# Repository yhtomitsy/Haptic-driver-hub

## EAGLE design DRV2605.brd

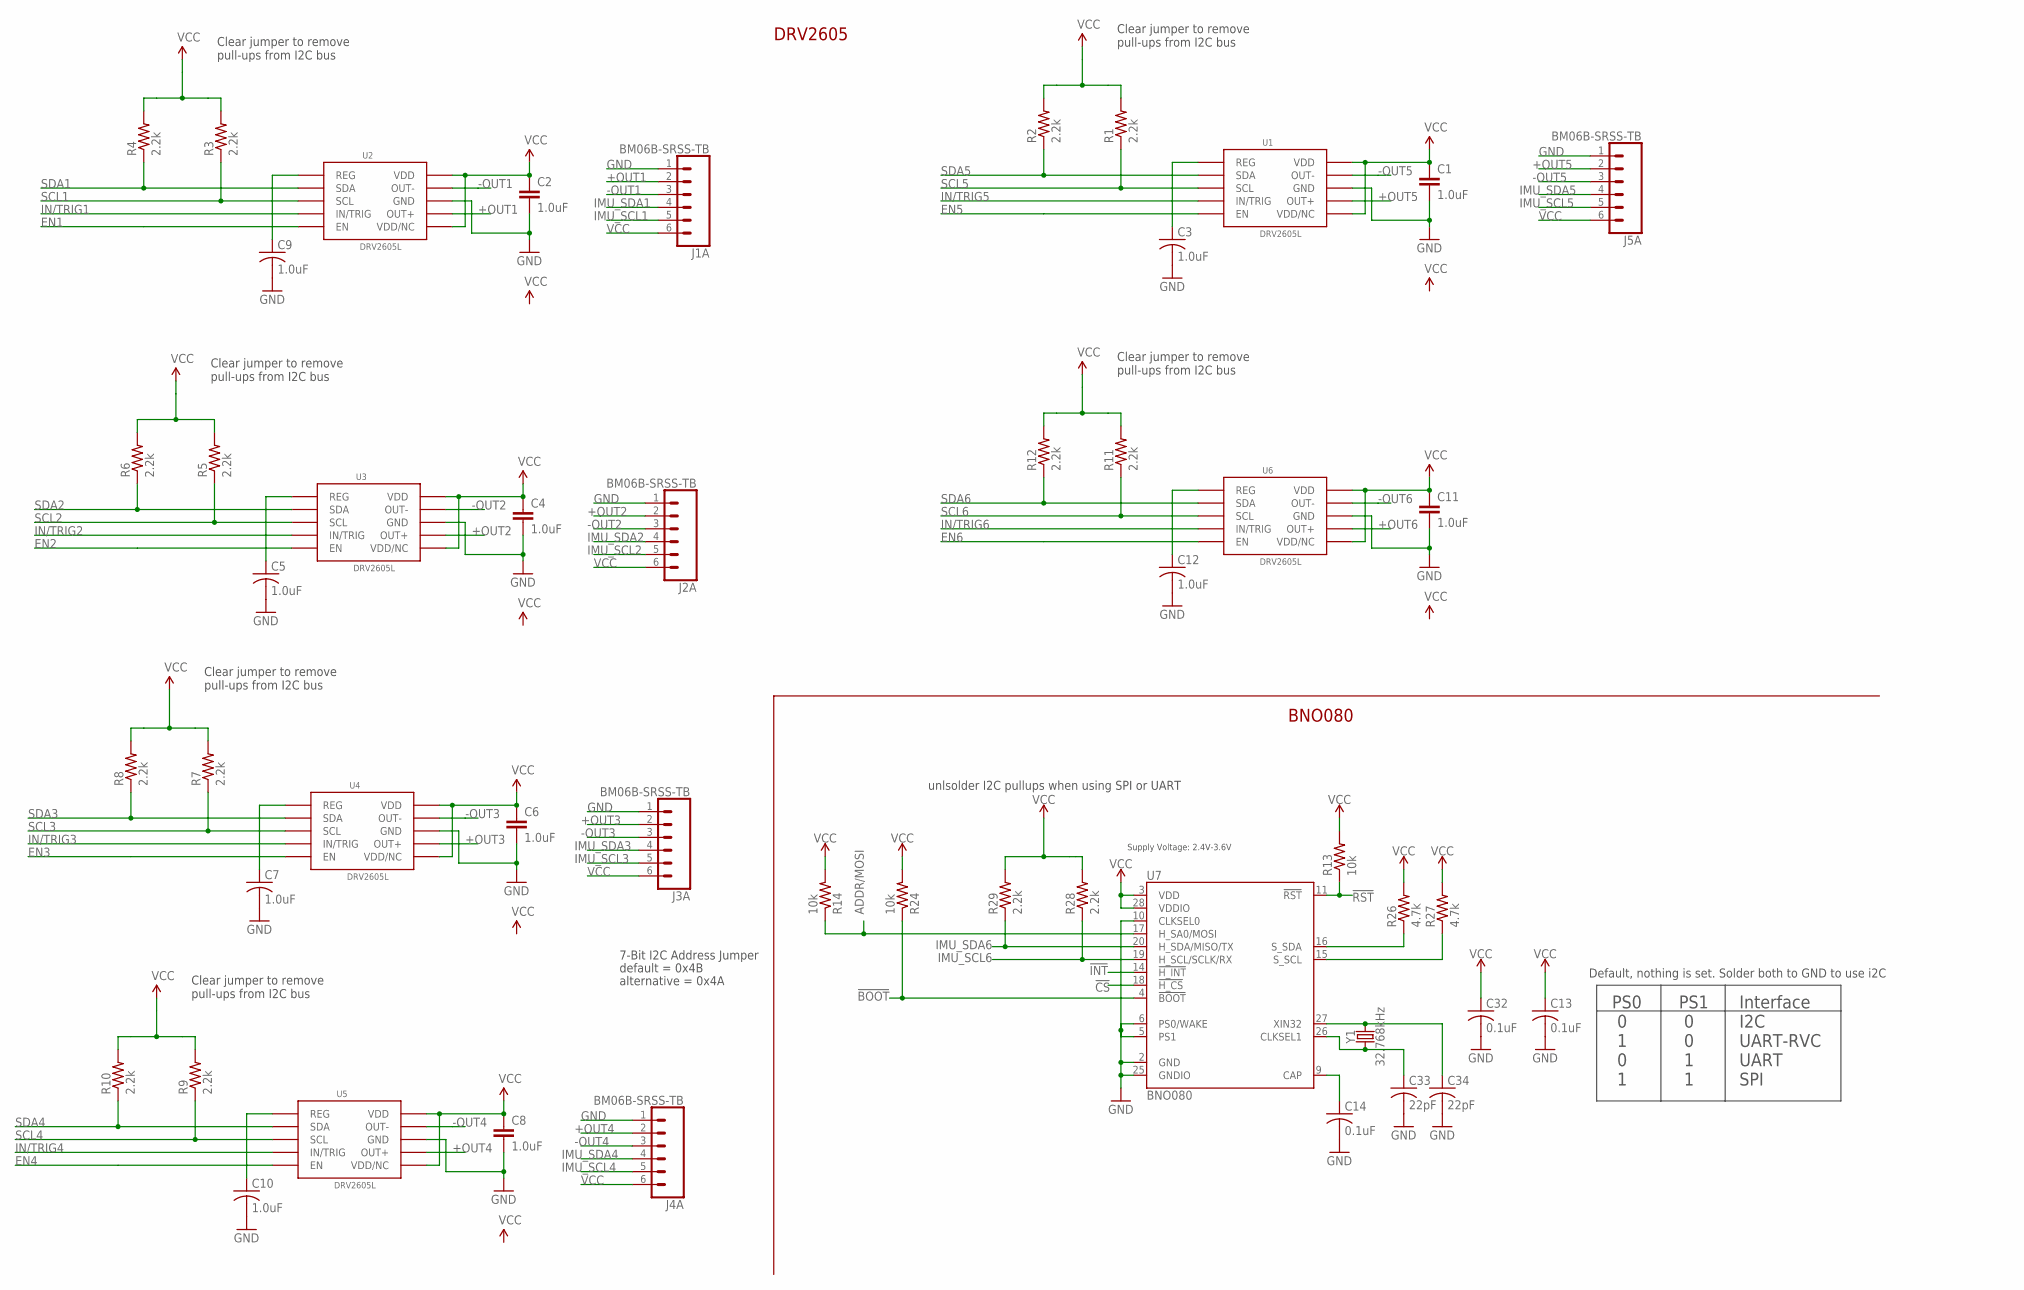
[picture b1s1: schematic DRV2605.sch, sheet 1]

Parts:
C1, C2, C4, C6, C8, C11: 1.0uF; 0402-CAP
C3, C5, C7, C9, C10, C12: 1.0uF; C0402
C13, C14, C32: 0.1uF; C0402
C33, C34: 22pF; C0402
J1, J2, J3, J4, J5: BM06B-SRSS-TB; JST-6-SMD-HORI-1.0MM
R1, R2, R3, R4, R5, R6, R7, R8, R9, R10, R11, R12: 2.2k; 0603-RES
R13, R14, R24: 10k; R0402
R26, R27: 4.7k; R0402
R28, R29: 2.2k; R0402
U1, U2, U3, U4, U5, U6: DRV2605L; VSSOP-10
U7: BNO080; LGA-28
Y1: 32.768kHz; CRYSTAL-SMD-3.2X1.5MM

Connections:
!BOOT: R24.1, U7.4 (!BOOT)
!CS: U7.18 (!H_CS)
!INT: U7.14 (!H_INT)
!RST: R13.1, U7.11 (!RST)
+OUT1: J1.2, U2.P$7 (OUT+)
+OUT2: J2.2, U3.P$7 (OUT+)
+OUT3: J3.2, U4.P$7 (OUT+)
+OUT4: J4.2, U5.P$7 (OUT+)
+OUT5: J5.2, U1.P$7 (OUT+)
+OUT6: U6.P$7 (OUT+); also elsewhere on the board
-OUT1: J1.3, U2.P$9 (OUT-)
-OUT2: J2.3, U3.P$9 (OUT-)
-OUT3: J3.3, U4.P$9 (OUT-)
-OUT4: J4.3, U5.P$9 (OUT-)
-OUT5: J5.3, U1.P$9 (OUT-)
-OUT6: U6.P$9 (OUT-); also elsewhere on the board
ADDR/MOSI: R14.1, U7.17 (H_SA0/MOSI)
CAP: C14.1, U7.9 (CAP)
EN1: U2.P$5 (EN); also elsewhere on the board
EN2: U3.P$5 (EN); also elsewhere on the board
EN3: U4.P$5 (EN); also elsewhere on the board
EN4: U5.P$5 (EN); also elsewhere on the board
EN5: U1.P$5 (EN); also elsewhere on the board
EN6: U6.P$5 (EN); also elsewhere on the board
GND: C1.2, C2.2, C3.2, C4.2, C5.2, C6.2, C7.2, C8.2, C9.2, C10.2, C11.2, C12.2, C13.2, C14.2, C32.2, C33.2, C34.2, J1.1, J2.1, J3.1, J4.1, J5.1, U1.P$8 (GND), U2.P$8 (GND), U3.P$8 (GND), U4.P$8 (GND), U5.P$8 (GND), U6.P$8 (GND), U7.2 (GND), U7.5 (PS1), U7.6 (PS0/WAKE), U7.10 (CLKSEL0), U7.25 (GNDIO); also elsewhere on the board
IMU_SCL1: J1.5; also elsewhere on the board
IMU_SCL2: J2.5; also elsewhere on the board
IMU_SCL3: J3.5; also elsewhere on the board
IMU_SCL4: J4.5; also elsewhere on the board
IMU_SCL5: J5.5; also elsewhere on the board
IMU_SCL6: R28.1, U7.19 (H_SCL/SCLK/RX); also elsewhere on the board
IMU_SDA1: J1.4; also elsewhere on the board
IMU_SDA2: J2.4; also elsewhere on the board
IMU_SDA3: J3.4; also elsewhere on the board
IMU_SDA4: J4.4; also elsewhere on the board
IMU_SDA5: J5.4; also elsewhere on the board
IMU_SDA6: R29.1, U7.20 (H_SDA/MISO/TX); also elsewhere on the board
IN/TRIG1: U2.P$4 (IN/TRIG); also elsewhere on the board
IN/TRIG2: U3.P$4 (IN/TRIG); also elsewhere on the board
IN/TRIG3: U4.P$4 (IN/TRIG); also elsewhere on the board
IN/TRIG4: U5.P$4 (IN/TRIG); also elsewhere on the board
IN/TRIG5: U1.P$4 (IN/TRIG); also elsewhere on the board
IN/TRIG6: U6.P$4 (IN/TRIG); also elsewhere on the board
unnamed: C3.1, U1.P$1 (REG)
unnamed: C12.1, U6.P$1 (REG)
unnamed: C34.1, U7.27 (XIN32), Y1.P$2 (2)
unnamed: C9.1, U2.P$1 (REG)
unnamed: C5.1, U3.P$1 (REG)
unnamed: C33.1, U7.26 (CLKSEL1), Y1.P$1 (1)
unnamed: C7.1, U4.P$1 (REG)
unnamed: C10.1, U5.P$1 (REG)
SCL1: R3.1, U2.P$2 (SCL); also elsewhere on the board
SCL2: R5.1, U3.P$2 (SCL); also elsewhere on the board
SCL3: R7.1, U4.P$2 (SCL); also elsewhere on the board
SCL4: R9.1, U5.P$2 (SCL); also elsewhere on the board
SCL5: R1.1, U1.P$2 (SCL); also elsewhere on the board
SCL6: R11.1, U6.P$2 (SCL); also elsewhere on the board
SDA1: R4.1, U2.P$3 (SDA); also elsewhere on the board
SDA2: R6.1, U3.P$3 (SDA); also elsewhere on the board
SDA3: R8.1, U4.P$3 (SDA); also elsewhere on the board
SDA4: R10.1, U5.P$3 (SDA); also elsewhere on the board
SDA5: R2.1, U1.P$3 (SDA); also elsewhere on the board
SDA6: R12.1, U6.P$3 (SDA); also elsewhere on the board
S_SCL: R27.1, U7.15 (S_SCL)
S_SDA: R26.1, U7.16 (S_SDA)
VCC: C1.1, C2.1, C4.1, C6.1, C8.1, C11.1, C13.1, C32.1, J1.6, J2.6, J3.6, J4.6, J5.6, R1.2, R2.2, R3.2, R4.2, R5.2, R6.2, R7.2, R8.2, R9.2, R10.2, R11.2, R12.2, R13.2, R14.2, R24.2, R26.2, R27.2, R28.2, R29.2, U1.P$6 (VDD/NC), U1.P$10 (VDD), U2.P$6 (VDD/NC), U2.P$10 (VDD), U3.P$6 (VDD/NC), U3.P$10 (VDD), U4.P$6 (VDD/NC), U4.P$10 (VDD), U5.P$6 (VDD/NC), U5.P$10 (VDD), U6.P$6 (VDD/NC), U6.P$10 (VDD), U7.3 (VDD), U7.28 (VDDIO); also elsewhere on the board

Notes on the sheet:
Clear jumper to remove pull-ups from I2C bus
7-Bit I2C Address Jumper
alternative = 0x4A
default = 0x4B
PS0 0 1 0 1
PS1 0 0 1 1
Interface I2C UART-RVC UART SPI
Default, nothing is set. Solder both to GND to use i2C
unlsolder I2C pullups when using SPI or UART
Supply Voltage: 2.4V-3.6V
BNO080
DRV2605

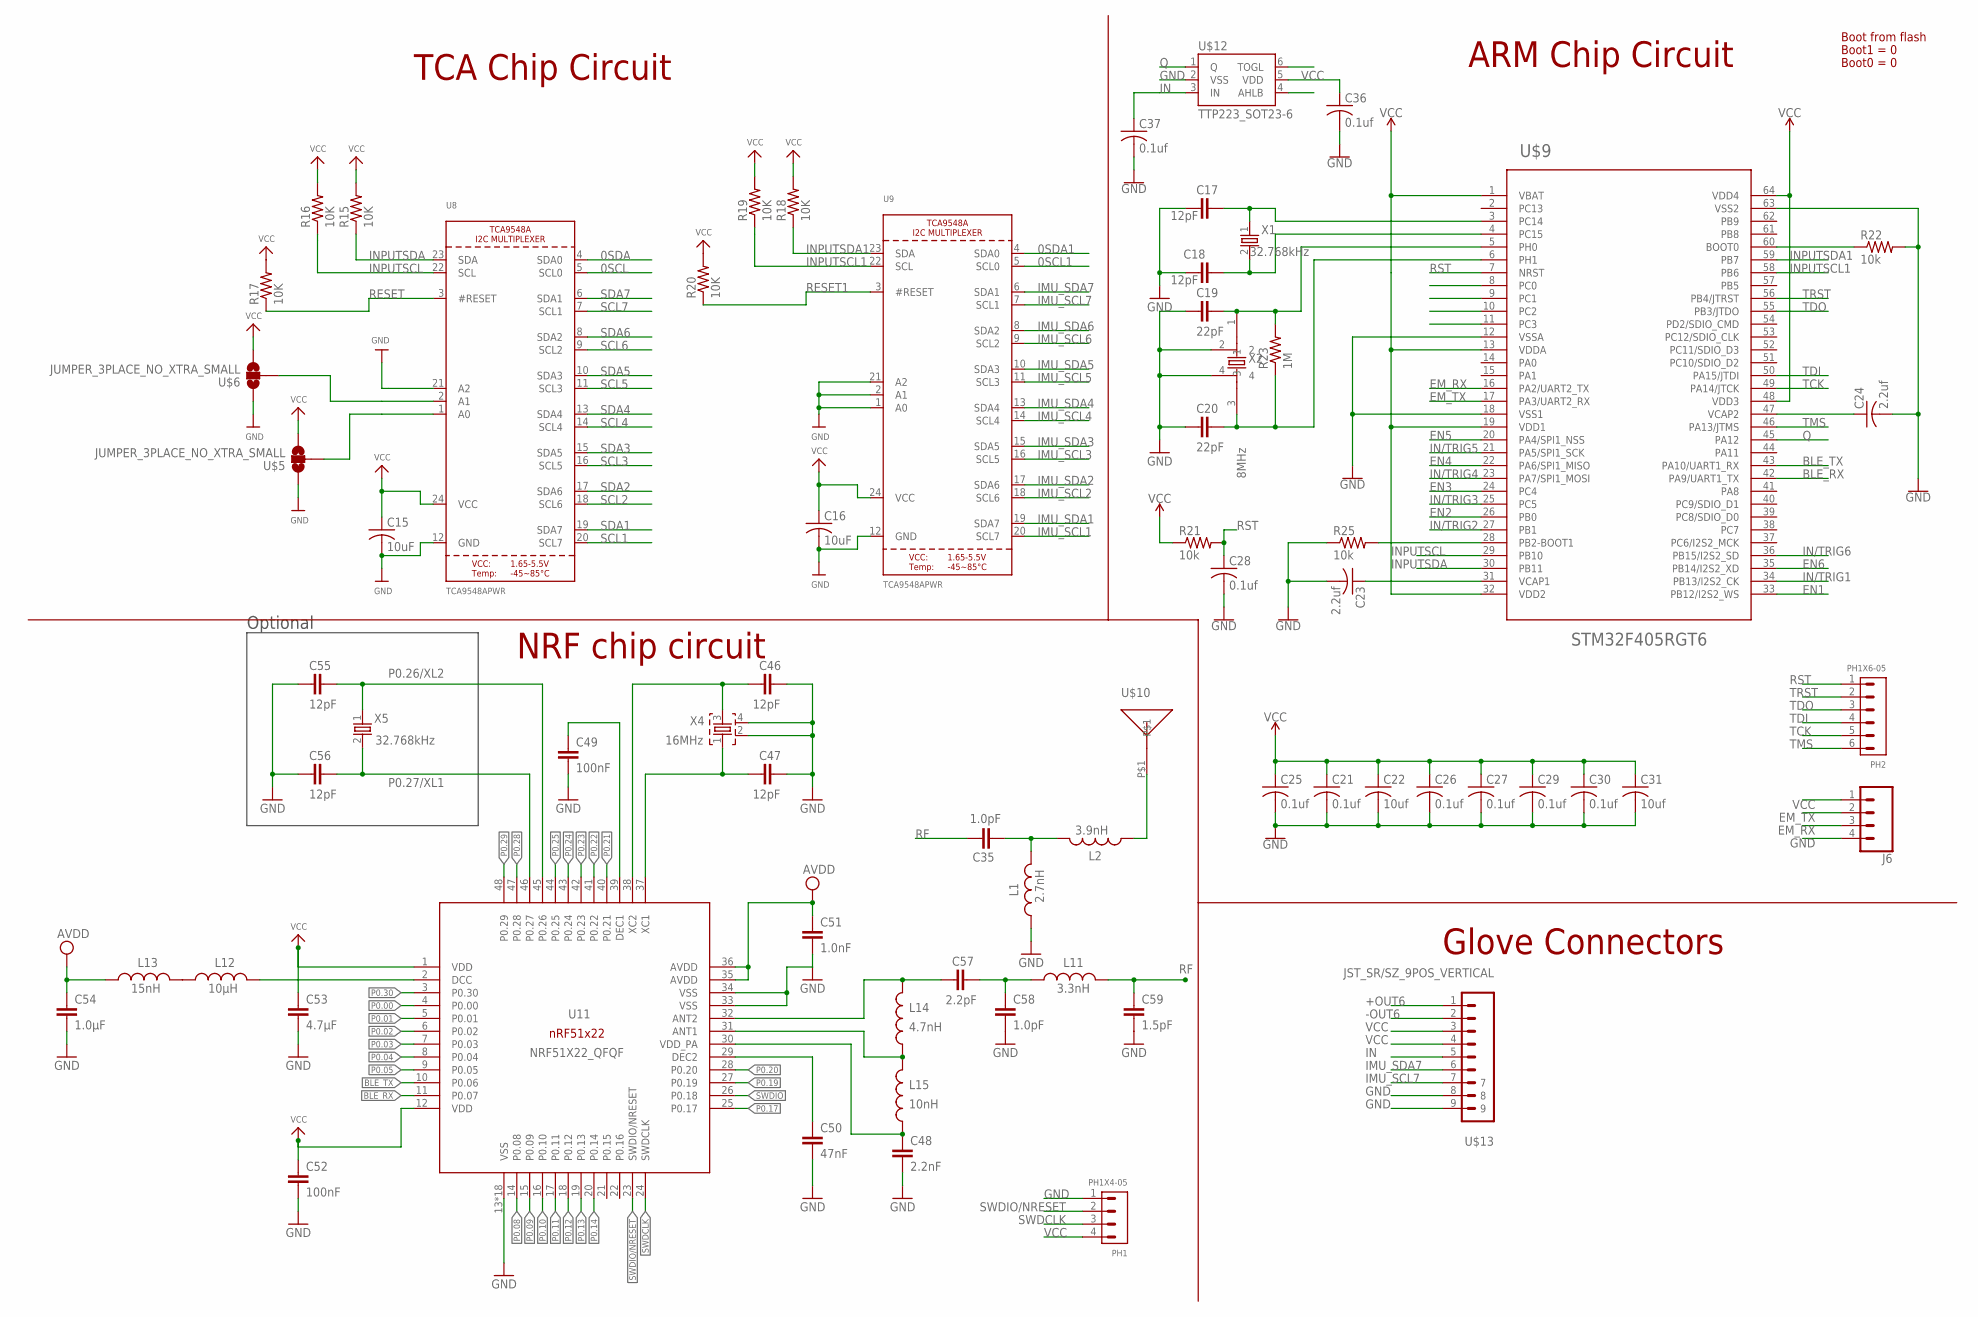
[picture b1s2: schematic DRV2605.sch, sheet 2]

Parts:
C15, C16: 10uF; C0402
C17, C18, C46, C47, C55, C56: 12pF; RESC0402_N
C19, C20: 22pF; RESC0402_N
C21, C25, C26, C27, C28, C29, C30, C36, C37: 0.1uf; C0402
C22, C31: 10uf; C0402
C23, C24: 2.2uf; C0402
C35, C58: 1.0pF; RESC0402_N
C48: 2.2nF; RESC0402_N
C49, C52: 100nF; RESC0402_N
C50: 47nF; RESC0402_N
C51: 1.0nF; RESC0402_N
C53: 4.7µF; RESC0603_N
C54: 1.0µF; RESC0603_N
C57: 2.2pF; RESC0402_N
C59: 1.5pF; RESC0402_N
J6: CONN_04; 1X04
L1: 2.7nH; RESC0402_N
L2: 3.9nH; RESC0402_N
L11: 3.3nH; RESC0402_N
L12: 10µH; RESC0603_N
L13: 15nH; RESC0402_N
L14: 4.7nH; RESC0402_N
L15: 10nH; RESC0402_N
PH1: PH1X4-05; PH005-1-4
PH2: PH1X6-05; PH005-1-6
R15, R16, R17, R18, R19, R20: 10K; R0402
R21, R22, R25: 10k; R0402
R23: 1M; R0402
U8, U9: TCA9548APWR; TSSOP24
U11: NRF51X22_QFQF; QFN40P600X600X90-48_N
U$5, U$6: JUMPER_3PLACE_NO_XTRA_SMALL; XTRA_SMALL_JUMPER_3_NO
U$9: STM32F405RGT6; TQFP64
U$10: ANT_2450AT18B100E; 2450AT18B100E
U$12: TTP223_SOT23-6; SOT23-6
U$13: JST_SR/SZ_9POS_VERTICAL; JST_SR/SZ_VERTICA_9POS
X1, X5: 32.768kHz; XTAL_3215_N
X2: 8MHz; CRYSTAL-SMD-5X3.2-4PAD
X4: 16MHz; BT-XTAL_2016_N

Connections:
0SCL: U8.5 (SCL0)
0SCL1: U9.5 (SCL0)
0SDA: U8.4 (SDA0)
0SDA1: U9.4 (SDA0)
+OUT6: U$13.1; also elsewhere on the board
-OUT6: U$13.2; also elsewhere on the board
AVDD: C51.1, C54.1, L13.1, U11.35 (AVDD), U11.36 (AVDD)
BLE_RX: U11.11 (P0.07), U$9.42 (PA9/UART1_TX)
BLE_TX: U11.10 (P0.06), U$9.43 (PA10/UART1_RX)
EM_RX: J6.3, U$9.16 (PA2/UART2_TX)
EM_TX: J6.2, U$9.17 (PA3/UART2_RX)
EN1: U$9.33 (PB12/I2S2_WS); also elsewhere on the board
EN2: U$9.26 (PB0); also elsewhere on the board
EN3: U$9.24 (PC4); also elsewhere on the board
EN4: U$9.22 (PA6/SPI1_MISO); also elsewhere on the board
EN5: U$9.20 (PA4/SPI1_NSS); also elsewhere on the board
EN6: U$9.35 (PB14/I2S2_XD); also elsewhere on the board
GND: C15.2, C16.2, C17.1, C18.1, C19.1, C20.1, C21.2, C22.2, C23.2, C24.2, C25.2, C26.2, C27.2, C28.2, C29.2, C30.2, C31.2, C36.2, C37.2, C46.2, C47.2, C48.2, C49.2, C50.2, C51.2, C52.2, C53.2, C54.2, C55.1, C56.1, C58.2, C59.2, J6.4, L1.1, PH1.1, R22.2, R25.1, U8.12 (GND), U8.21 (A2), U9.1 (A0), U9.2 (A1), U9.12 (GND), U9.21 (A2), U11.13 (VSS), U11.33 (VSS), U11.34 (VSS), U11.PAD (VSS), U11.PAD@VIA01 (VSS), U11.PAD@VIA02 (VSS), U11.PAD@VIA03 (VSS), U11.PAD@VIA04 (VSS), U11.PAD@VIA05 (VSS), U11.PAD@VIA06 (VSS), U11.PAD@VIA07 (VSS), U11.PAD@VIA08 (VSS), U11.PAD@VIA09 (VSS), U11.PAD@VIA10 (VSS), U11.PAD@VIA11 (VSS), U11.PAD@VIA12 (VSS), U11.PAD@VIA13 (VSS), U11.PAD@VIA14 (VSS), U11.PAD@VIA15 (VSS), U11.PAD@VIA16 (VSS), U$5.1, U$6.1, U$9.12 (VSSA), U$9.18 (VSS1), U$9.63 (VSS2), U$12.2 (VSS), U$13.8, U$13.9, X2.2, X2.4, X4.2, X4.4; also elsewhere on the board
IMU_SCL1: U9.20 (SCL7); also elsewhere on the board
IMU_SCL2: U9.18 (SCL6); also elsewhere on the board
IMU_SCL3: U9.16 (SCL5); also elsewhere on the board
IMU_SCL4: U9.14 (SCL4); also elsewhere on the board
IMU_SCL5: U9.11 (SCL3); also elsewhere on the board
IMU_SCL6: U9.9 (SCL2); also elsewhere on the board
IMU_SCL7: U9.7 (SCL1), U$13.7
IMU_SDA1: U9.19 (SDA7); also elsewhere on the board
IMU_SDA2: U9.17 (SDA6); also elsewhere on the board
IMU_SDA3: U9.15 (SDA5); also elsewhere on the board
IMU_SDA4: U9.13 (SDA4); also elsewhere on the board
IMU_SDA5: U9.10 (SDA3); also elsewhere on the board
IMU_SDA6: U9.8 (SDA2); also elsewhere on the board
IMU_SDA7: U9.6 (SDA1), U$13.6
IN: C37.1, U$12.3 (IN), U$13.5
IN/TRIG1: U$9.34 (PB13/I2S2_CK); also elsewhere on the board
IN/TRIG2: U$9.27 (PB1); also elsewhere on the board
IN/TRIG3: U$9.25 (PC5); also elsewhere on the board
IN/TRIG4: U$9.23 (PA7/SPI1_MOSI); also elsewhere on the board
IN/TRIG5: U$9.21 (PA5/SPI1_SCK); also elsewhere on the board
IN/TRIG6: U$9.36 (PB15/I2S2_SD); also elsewhere on the board
INPUTSCL: R16.1, U8.22 (SCL), U$9.29 (PB10)
INPUTSCL1: R19.1, U9.22 (SCL), U$9.58 (PB6)
INPUTSDA: R15.1, U8.23 (SDA), U$9.30 (PB11)
INPUTSDA1: R18.1, U9.23 (SDA), U$9.59 (PB7)
unnamed: R25.2, U$9.28 (PB2-BOOT1)
unnamed: R22.1, U$9.60 (BOOT0)
unnamed: C23.1, U$9.31 (VCAP1)
unnamed: C24.1, U$9.47 (VCAP2)
unnamed: C35.1, L1.2, L2.2
unnamed: L2.1, U$10.P$1
unnamed: U8.1 (A0), U$5.2
unnamed: U8.2 (A1), U$6.2
unnamed: C46.1, U11.38 (XC2), X4.3
unnamed: L12.1, L13.2
unnamed: L12.2, U11.2 (DCC)
unnamed: C50.1, U11.29 (DEC2)
unnamed: C49.1, U11.39 (DEC1)
unnamed: L14.1, L15.2, U11.31 (ANT1)
unnamed: C48.1, L15.1, U11.30 (VDD_PA)
unnamed: C57.1, L14.2, U11.32 (ANT2)
unnamed: C57.2, C58.1, L11.1
P0.00: U11.4 (P0.00)
P0.01: U11.5 (P0.01)
P0.02: U11.6 (P0.02)
P0.03: U11.7 (P0.03)
P0.04: U11.8 (P0.04)
P0.05: U11.9 (P0.05)
P0.08: U11.14 (P0.08)
P0.09: U11.15 (P0.09)
P0.10: U11.16 (P0.10)
P0.11: U11.17 (P0.11)
P0.12: U11.18 (P0.12)
P0.13: U11.19 (P0.13)
P0.14: U11.20 (P0.14)
P0.17: U11.25 (P0.17)
P0.19: U11.27 (P0.19)
P0.20: U11.28 (P0.20)
P0.21: U11.40 (P0.21)
P0.22: U11.41 (P0.22)
P0.23: U11.42 (P0.23)
P0.24: U11.43 (P0.24)
P0.25: U11.44 (P0.25)
P0.26/XL2: C55.2, U11.45 (P0.26), X5.1
P0.27/XL1: C56.2, U11.46 (P0.27), X5.2
P0.28: U11.47 (P0.28)
P0.29: U11.48 (P0.29)
P0.30: U11.3 (P0.30)
PC14: C17.2, U$9.3 (PC14), X1.1
PC15: C18.2, U$9.4 (PC15), X1.2
PH0: C19.2, R23.2, U$9.5 (PH0), X2.1
PH1: C20.2, R23.1, U$9.6 (PH1), X2.3
Q: U$9.45 (PA12), U$12.1 (Q)
RESET: R17.1, U8.3 (#RESET)
RESET1: R20.1, U9.3 (#RESET)
RF: C35.2, C59.1, L11.2
RST: C28.1, PH2.1, R21.2, U$9.7 (NRST)
SCL1: U8.20 (SCL7); also elsewhere on the board
SCL2: U8.18 (SCL6); also elsewhere on the board
SCL3: U8.16 (SCL5); also elsewhere on the board
SCL4: U8.14 (SCL4); also elsewhere on the board
SCL5: U8.11 (SCL3); also elsewhere on the board
SCL6: U8.9 (SCL2); also elsewhere on the board
SCL7: U8.7 (SCL1)
SDA1: U8.19 (SDA7); also elsewhere on the board
SDA2: U8.17 (SDA6); also elsewhere on the board
SDA3: U8.15 (SDA5); also elsewhere on the board
SDA4: U8.13 (SDA4); also elsewhere on the board
SDA5: U8.10 (SDA3); also elsewhere on the board
SDA6: U8.8 (SDA2); also elsewhere on the board
SDA7: U8.6 (SDA1)
SWDCLK: PH1.3, U11.24 (SWDCLK)
SWDIO: U11.26 (P0.18)
SWDIO/NRESET: PH1.2, U11.23 (SWDIO/NRESET)
TCK: PH2.5, U$9.49 (PA14/JTCK)
TDI: PH2.4, U$9.50 (PA15/JTDI)
TDO: PH2.3, U$9.55 (PB3/JTDO)
TMS: PH2.6, U$9.46 (PA13/JTMS)
TRST: PH2.2, U$9.56 (PB4/JTRST)
VCC: C15.1, C16.1, C21.1, C22.1, C25.1, C26.1, C27.1, C29.1, C30.1, C31.1, C36.1, C52.1, C53.1, J6.1, PH1.4, R15.2, R16.2, R17.2, R18.2, R19.2, R20.2, R21.1, U8.24 (VCC), U9.24 (VCC), U11.1 (VDD), U11.12 (VDD), U$5.3, U$6.3, U$9.1 (VBAT), U$9.13 (VDDA), U$9.19 (VDD1), U$9.32 (VDD2), U$9.48 (VDD3), U$9.64 (VDD4), U$12.5 (VDD), U$13.3, U$13.4; also elsewhere on the board
X2: C47.1, U11.37 (XC1), X4.1

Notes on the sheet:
NRF chip circuit
TCA Chip Circuit
Optional
Boot1 = 0
Boot0 = 0
Boot from flash
ARM Chip Circuit
Glove Connectors

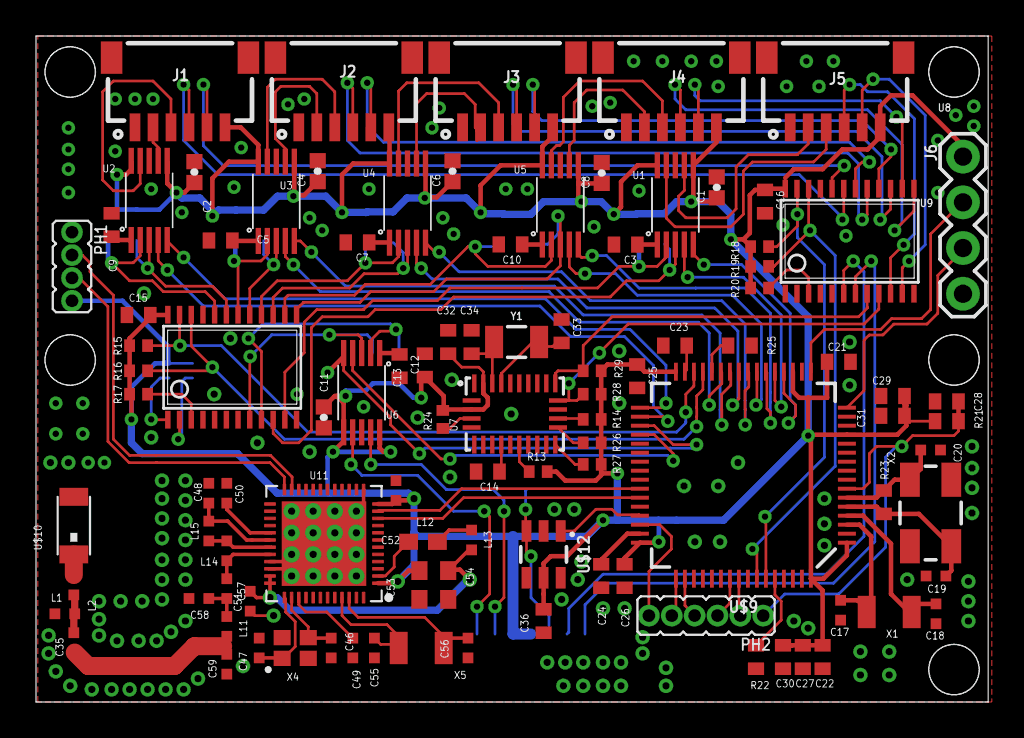
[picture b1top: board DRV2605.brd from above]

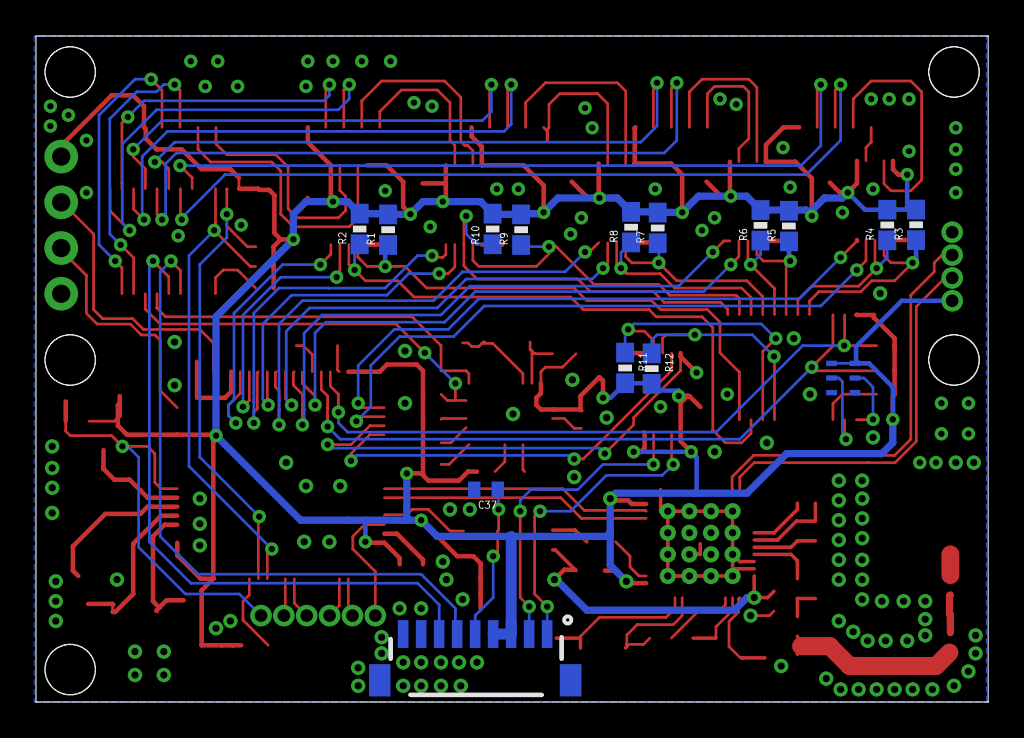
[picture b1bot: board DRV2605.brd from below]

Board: 2 copper layers, 52.9 x 37.0 mm, 116 parts (16 on the bottom side), 112 nets.

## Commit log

2018-10-06 board placement for first DRV
2018-10-06 6 done with airwires
2018-10-08 DRV routing done
2018-10-08 TCA added and routed to 5 fingers
2018-10-09 working on control pins
2018-10-10 NRF done STM in progress
2018-10-11 6DRVs ARM - done; IMU on board
2018-10-11 6DRVs ARM IMU on board - done
2018-10-11 6DRVs ARM IMU on board - done; palmIMU/battery/programming connector
2018-10-11 glove connector;programming pins;NRF antenna left
2018-10-12 glove connector;programming pins;NRF antenna
2018-10-12 NRF antenna yet to be done; glove 50mm wide
2018-10-13 board done awaiting validation

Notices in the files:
parts and their libraries:
SparkFun-Capacitors: Licensing: Creative Commons ShareAlike 4.0 International - https://creativecommons.org/licenses/by-sa/4.0
microbuilder: This work is placed in the public domain, and may be freely used for commercial and non-commercial work with the following conditions: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
